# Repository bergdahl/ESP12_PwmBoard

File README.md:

# ESP12_PwmBoard

This is a simple ESP-12 based 4 channel PWM board I designed to be used in Home Assistant. It is powered by 5V over a micro USB connector, and gives you 4 channels of PWM control, perfect to control analog  LED strips at 24 or 12 Volts. The screw connectors used are rated at maximum 15A, so you need to keep the _total_ combined power usage under that limit. The MOSFET's used are way overkill (100V/36A), they just happened to be what I had in stock.

I designed the board to be used with dual LED strips, warm and cold white, which gives you 2 channels with color temperature control in Home Assistant, but it can be used as a 4 channel PwM controller as well.

> NOTE: This PCB is NOT designed to be used for mains voltage!

## PCB files

I have added the Gerber files in the `PCB/Gerber` folder, just zip and upload to your favorite PCB manufacturer.

I have also included the EAGLE design files if you need to modify the design for yoyr needs.

## Terminal connector pinout

GND / VCC | CH1-1 / CH1-2 / VCC | CH2-1 / CH2-2 / VCC

## Firmware

I use ESPHome to set it up, which is the easiest way for it to show up in Home Assistant. 

Change the `esphome` section to this:

```
esphome:
  name: pwm1
  platform: ESP8266
  board: esp12e
```
Add the following section to add the PWM controls as dimmable lights in Home Assistant.
```
output:
  - platform: esp8266_pwm
    pin: GPIO13
    id: output_pwm1
  - platform: esp8266_pwm
    pin: GPIO12
    id: output_pwm2
  - platform: esp8266_pwm
    pin: GPIO5
    id: output_pwm3
  - platform: esp8266_pwm
    pin: GPIO4
    id: output_pwm4
    
light:
  - platform: monochromatic
    name: "pwm1"
    output: "output_pwm1"
  - platform: monochromatic
    name: "pwm2"
    output: "output_pwm2"
  - platform: monochromatic
    name: "pwm3"
    output: "output_pwm3"
  - platform: monochromatic
    name: "pwm4"
    output: "output_pwm4"
```

You can optionally setup your strips as color controllable, for use with dual color LED strips, or two strips with different color values inside the same stip enclosure. 
Add the following section to add the PWM controls as 2 channels with cold/warm white lights in Home Assistant. Substitute the color temperature values for your LED strips.

```
output:
  - platform: esp8266_pwm
    pin: GPIO13
    id: output_pwm1_c
  - platform: esp8266_pwm
    pin: GPIO12
    id: output_pwm1_w
  - platform: esp8266_pwm
    pin: GPIO5
    id: output_pwm2_c
  - platform: esp8266_pwm
    pin: GPIO4
    id: output_pwm2_w
    
light:
  - platform: cwww
    name: "pwm1"
    cold_white: output_pwm1_c
    warm_white: output_pwm1_w
    cold_white_color_temperature: 4000 K
    warm_white_color_temperature: 3000 K
  - platform: cwww
    name: "pwm2"
    cold_white: output_pwm2_c
    warm_white: output_pwm2_w
    cold_white_color_temperature: 4000 K
    warm_white_color_temperature: 3000 K
    constant_brightness: true
```

### Flashing the board

You will need a USB-Serial adapter for initial upload of the firmware, and use the [ESPHome-Flasher](https://github.com/esphome/esphome-flasher) flashing utility.

 - Compile and download the firmware to your local machine.
 - Connect the serial adapter to the board, the board is designed for the pinout of standard FT232RL adapters.
 - Hold down the BOOT button, tap the RST button and then let go of RST. This puts the ESP-12 module in bootloader mode ready for firmware upload.
 - Start ESPHome-Flasher, select the firmware file and the proper COM port and click _Flash ESP_.

## Enclosure

I designed a simple enclosure for 3D printing, available as STL files in the `Enclosure` folder. 

I also included the Fusion360 design file if you need to modify the design for your usage.

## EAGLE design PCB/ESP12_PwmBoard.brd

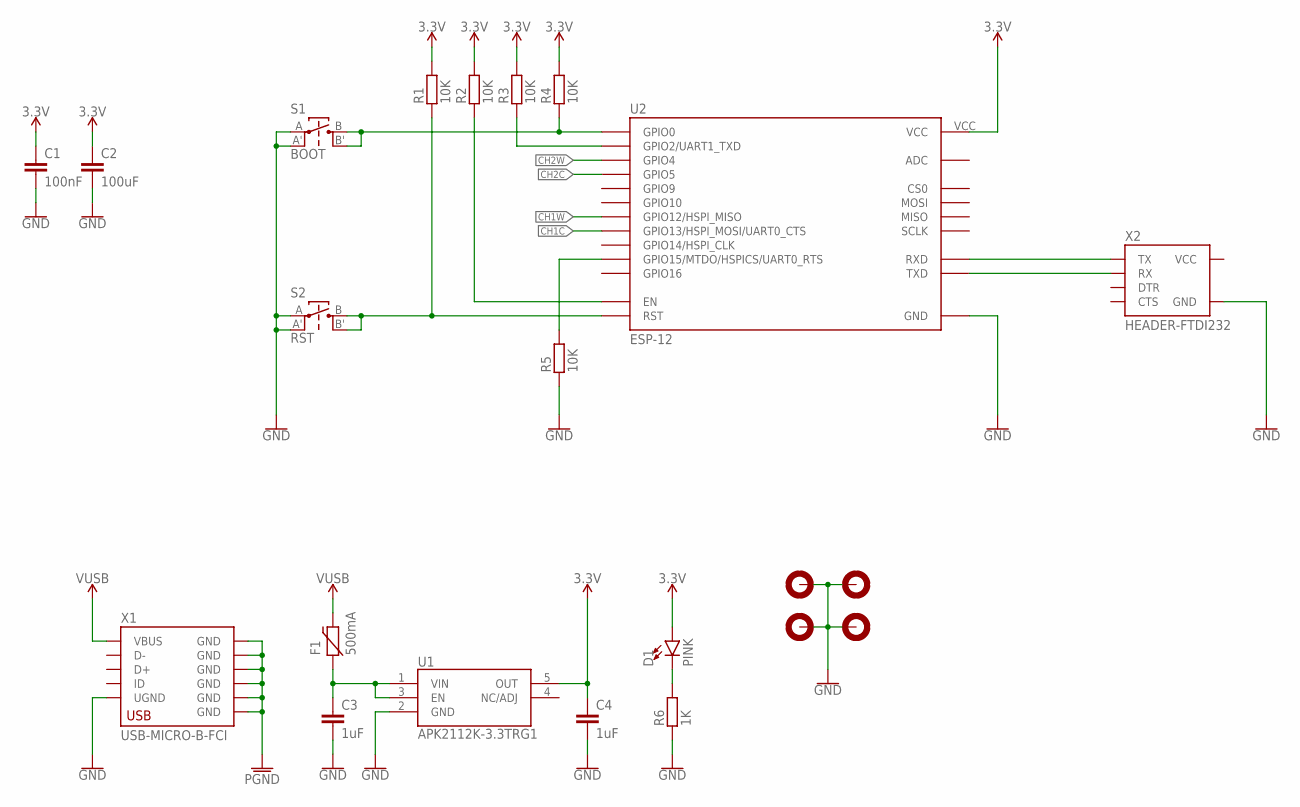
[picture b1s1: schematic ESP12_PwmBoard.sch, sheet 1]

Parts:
C1: 100nF; C0603
C2: 100uF; C0603
C3, C4: 1uF; C0603
D1: PINK; LED0603
F1: 500mA; PTC-0ZCJ-1206
H1, H2, H3, H4: MOUNTHOLE-PAD3.2; 3.2-PAD
R1, R2, R3, R4, R5: 10K; R0603
R6: 1K; R0603
S1: BOOT; TACT-SWITCH-EVQ
S2: RST; TACT-SWITCH-EVQ
U1: APK2112K-3.3TRG1; SOT23-5
U2: ESP-12; ESP-12E
X1: USB-MICRO-B-FCI
X2: HEADER-FTDI232; FTDI232-1X06

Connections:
3.3V: C1.1, C2.1, C4.1, D1.A, R1.2, R2.2, R3.2, R4.2, U1.5 (OUT), U2.VCC
CH1C: U2.GPIO13 (GPIO13/HSPI_MOSI/UART0_CTS); also elsewhere on the board
CH1W: U2.GPIO12 (GPIO12/HSPI_MISO); also elsewhere on the board
CH2C: U2.GPIO5; also elsewhere on the board
CH2W: U2.GPIO4; also elsewhere on the board
GND: C1.2, C2.2, C3.2, C4.2, H1.B3,2, H2.B3,2, H3.B3,2, H4.B3,2, R5.1, R6.1, S1.A, S1.A', S2.A, S2.A', U1.2 (GND), U2.GND, X1.5 (UGND), X2.GND; also elsewhere on the board
unnamed: R4.1, S1.B, S1.B', U2.GPIO0
unnamed: R1.1, S2.B, S2.B', U2.RST
unnamed: R2.1, U2.EN
unnamed: C3.1, F1.1, U1.1 (VIN), U1.3 (EN)
unnamed: R3.1, U2.GPIO2 (GPIO2/UART1_TXD)
unnamed: U2.RXD, X2.TX
unnamed: U2.TXD, X2.RX
unnamed: D1.C, R6.2
unnamed: R5.2, U2.GPIO15 (GPIO15/MTDO/HSPICS/UART0_RTS)
PGND: X1.GND@1 (GND), X1.GND@2 (GND), X1.GND@3 (GND), X1.GND@4 (GND), X1.GND@5 (GND), X1.GND@6 (GND)
VCC: X2.VCC
VUSB: F1.2, X1.1 (VBUS)

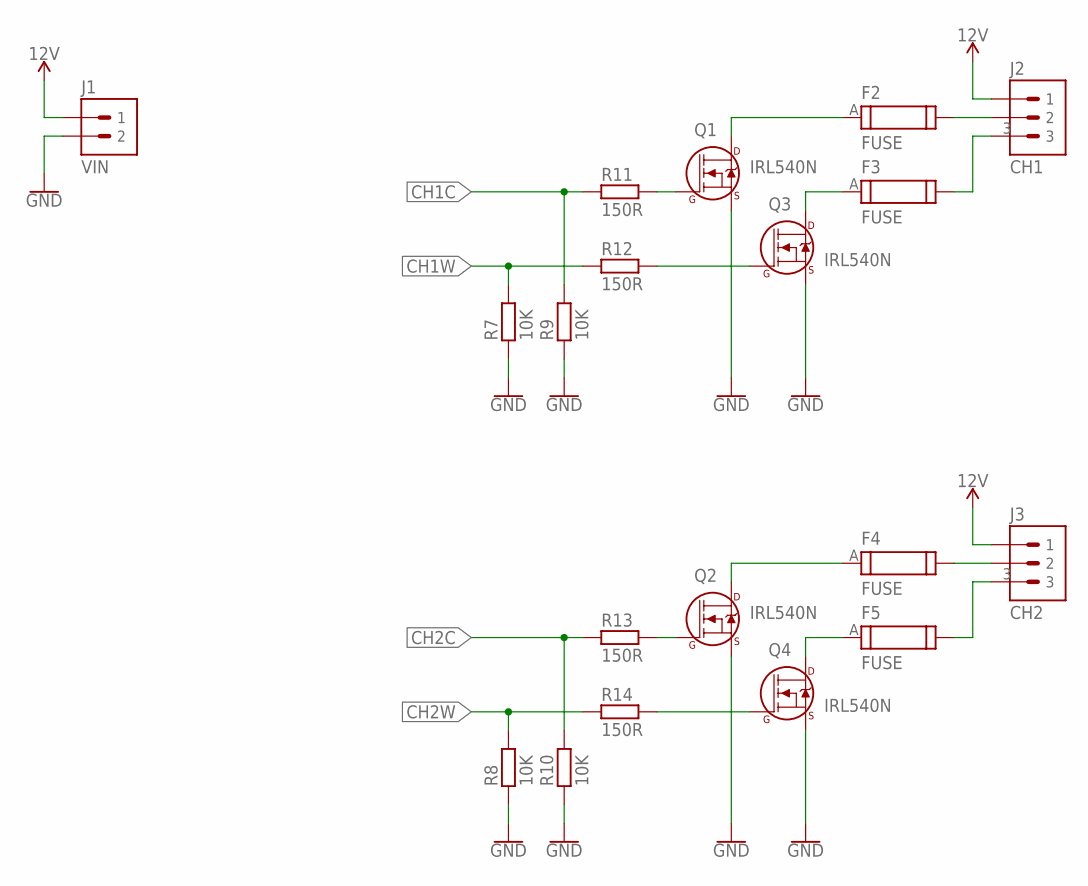
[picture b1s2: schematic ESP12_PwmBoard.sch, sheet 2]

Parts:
F2, F3, F4, F5: FUSE; FUSE-TEAL
J1: VIN; ONSHORE-OSTTC022162
J2: CH1; ONSHORE-OSTTC032162
J3: CH2; ONSHORE-OSTTC032162
Q1, Q2, Q3, Q4: IRL540N; TO-220AB
R7, R8, R9, R10: 10K; R0603
R11, R12, R13, R14: 150R; R0603

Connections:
12V: J1.1, J2.1, J3.1
CH1C: R9.2, R11.1; also elsewhere on the board
CH1W: R7.2, R12.1; also elsewhere on the board
CH2C: R10.2, R13.1; also elsewhere on the board
CH2W: R8.2, R14.1; also elsewhere on the board
GND: J1.2, Q1.3 (S), Q2.3 (S), Q3.3 (S), Q4.3 (S), R7.1, R8.1, R9.1, R10.1; also elsewhere on the board
unnamed: Q3.1 (G), R12.2
unnamed: Q1.1 (G), R11.2
unnamed: F3.A, Q3.2 (D)
unnamed: F2.A, Q1.2 (D)
unnamed: F3.B, J2.3
unnamed: F2.B, J2.2
unnamed: Q4.1 (G), R14.2
unnamed: Q2.1 (G), R13.2
unnamed: F5.A, Q4.2 (D)
unnamed: F4.A, Q2.2 (D)
unnamed: F5.B, J3.3
unnamed: F4.B, J3.2

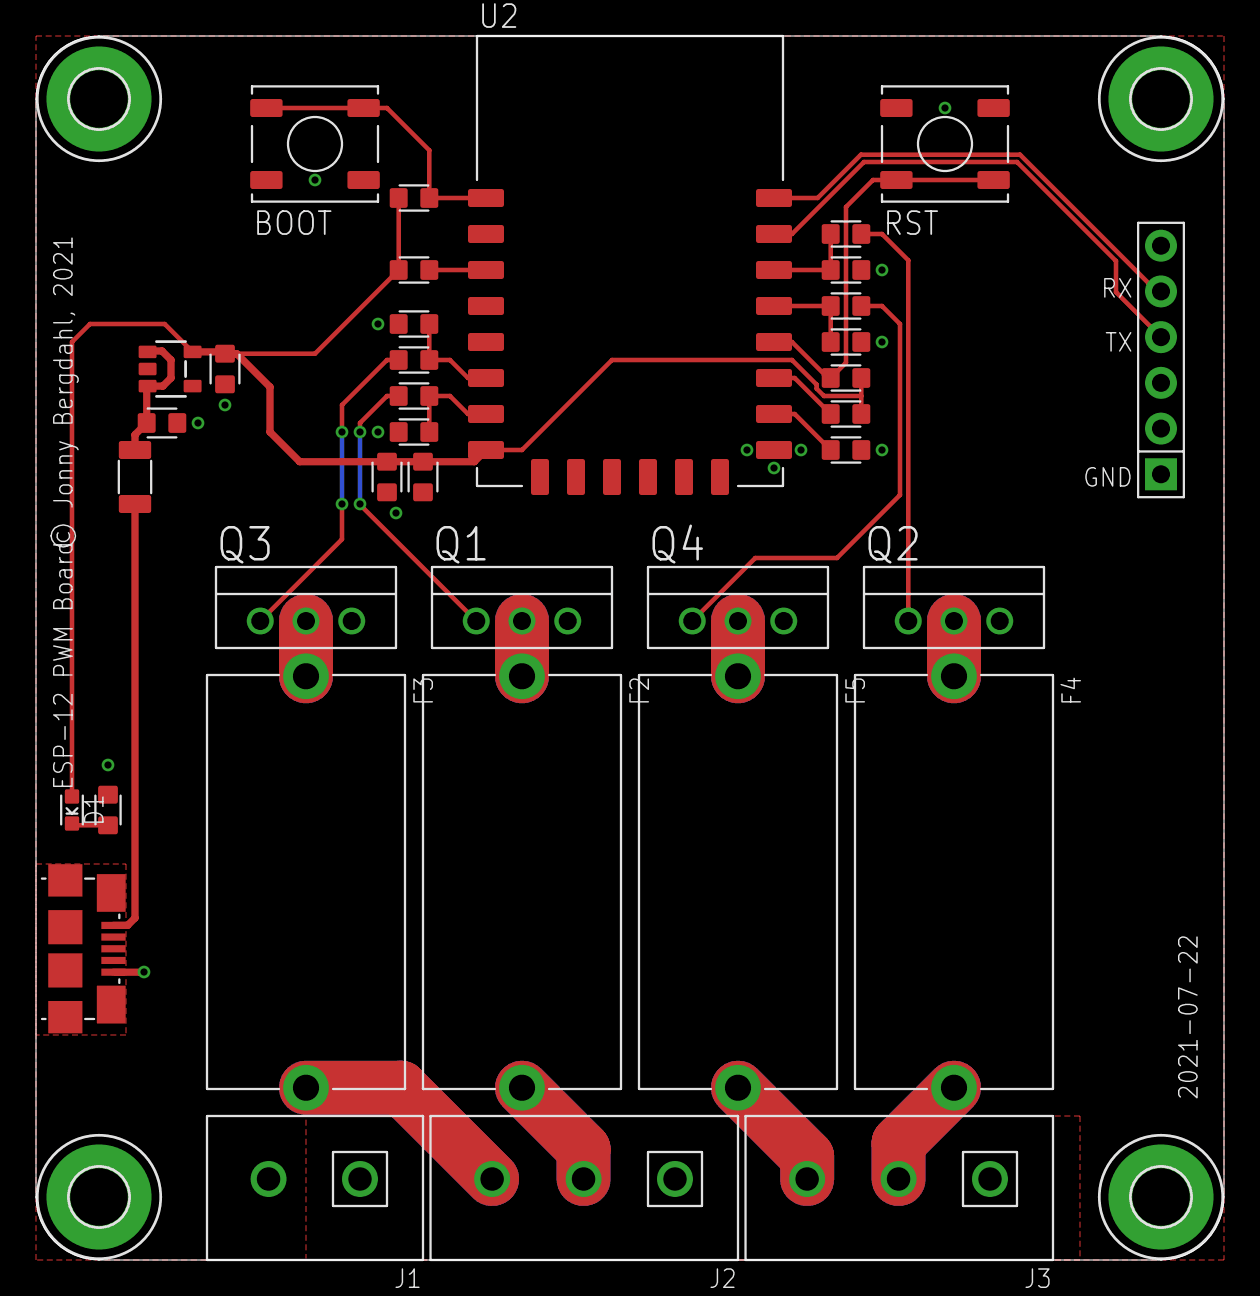
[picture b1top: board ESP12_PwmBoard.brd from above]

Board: 2 copper layers, 66.0 x 68.0 mm, 41 parts (0 on the bottom side), 30 nets.

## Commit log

2021-07-31 Added documentation
2021-07-31 Added measurements
2021-08-02 Added enclosure
2021-08-11 Add PDF
2021-09-11 Added non color control example

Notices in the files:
PCB/ESP12_PwmBoard.brd:
© Jonny Bergdahl, 2021
